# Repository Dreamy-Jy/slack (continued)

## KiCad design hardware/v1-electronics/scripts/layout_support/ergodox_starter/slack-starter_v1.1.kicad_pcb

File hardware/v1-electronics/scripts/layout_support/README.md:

This folder is a collection of code used to support the laying out of the keyboard components.

`ergogen_starter/` - is an [ergogen](https://ergogen.xyz/) config used to layout the base keyboard, most of this was ai generated.

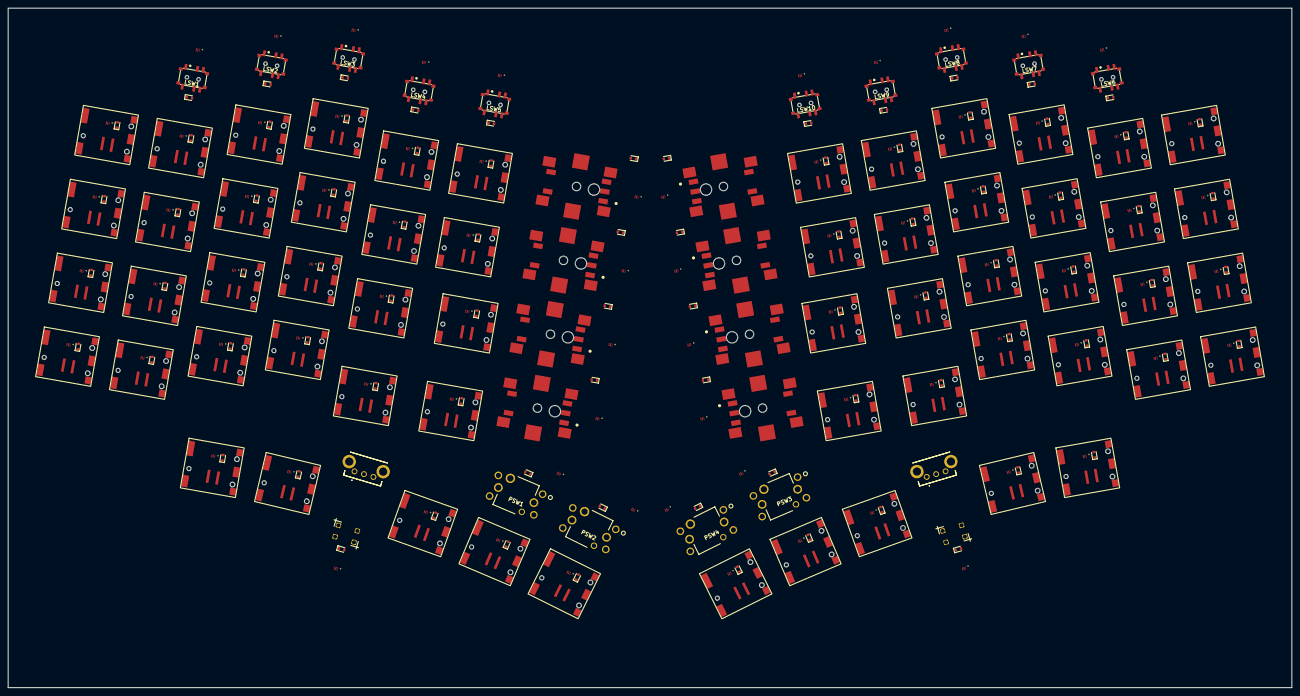
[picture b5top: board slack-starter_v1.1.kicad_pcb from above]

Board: 2 copper layers, 326.0 x 172.6 mm, 248 parts (0 on the bottom side), 165 nets, no tracks yet.

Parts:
D1, D2, D3, D4, D5, D6, D7, D8, D9, D10, D11, D12, D13, D14, D15, D16, D17, D18, D19, D20, D21, D22, D23, D24, D25, D26, D27, D28, D29, D30, D31, D32, D33, D34, D35, D36, D37, D38, D39, D40, D41, D42, D43, D44, D45, D46, D47, D48, D49, D50, D51, D52, D53, D54, D55, D56, D57, D58, D59, D60, D61, D62, D63, D64, D65, D66, D67, D68, D69, D70, D71, D72, D73, D74, D75, D76, D77, D78, D79, D80, D81, D82: D_SOD-523
ENC1, ENC2, ENC3, ENC4, ENC5, ENC6, ENC7, ENC8: PEC11S929KS0015
LED1, LED2, LED3, LED4, LED5, LED6, LED7, LED8, LED9, LED10, LED11, LED12, LED13, LED14, LED15, LED16, LED17, LED18, LED19, LED20, LED21, LED22, LED23, LED24, LED25, LED26, LED27, LED28, LED29, LED30, LED31, LED32, LED33, LED34, LED35, LED36, LED37, LED38, LED39, LED40, LED41, LED42, LED43, LED44, LED45, LED46, LED47, LED48, LED49, LED50, LED51, LED52, LED53, LED54, LED55, LED56, LED57, LED58, LED59, LED60, LED61, LED62, LED63, LED64, LED65, LED66, LED67, LED68, LED69, LED70, LED71, LED72, LED73, LED74, LED75, LED76, LED77, LED78, LED79, LED80, LED81, LED82: LTSTFC12WEGBD5A
LSW1, LSW2, LSW3, LSW4, LSW5, LSW6, LSW7, LSW8, LSW9, LSW10: SSSS820201
PSW1, PSW2, PSW3, PSW4: SPEF110100
S1, S2, S3, S4, S5, S6, S7, S8, S9, S10, S11, S12, S13, S14, S15, S16, S17, S18, S19, S20, S21, S22, S23, S24, S25, S26, S27, S28, S29, S30, S31, S32, S33, S34, S35, S36, S37, S38, S39, S40, S41, S42, S43, S44, S45, S46, S47, S48, S49, S50, S51, S52, S53, S54, S55, S56, S57, S58: Cherry_ULP_SMD
SCLK1, SCLK2: TC-1109-C-E
SCRL1, SCRL2: EC10E1220505

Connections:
C0: S1.1, S2.1, S3.1, S4.1, SCLK1.1
C1: LSW1.2, S5.1, S6.1, S7.1, S8.1, S25.1
C2: LSW2.2, S9.1, S10.1, S11.1, S12.1, S26.1
C3: LSW3.2, S13.1, S14.1, S15.1, S16.1, S27.1
C4: LSW4.2, S17.1, S18.1, S19.1, S20.1, S28.1
C5: LSW5.2, PSW1.1, S21.1, S22.1, S23.1, S24.1, S29.1
C6: LSW10.2, PSW2.1, S50.1, S51.1, S52.1, S53.1, S58.1
C7: LSW9.2, PSW4.1, S46.1, S47.1, S48.1, S49.1, S57.1
C8: LSW8.2, PSW3.1, S42.1, S43.1, S44.1, S45.1, S56.1
C9: LSW7.2, S38.1, S39.1, S40.1, S41.1, S55.1
C10: LSW6.2, S34.1, S35.1, S36.1, S37.1, S54.1
C11: S30.1, S31.1, S32.1, S33.1, SCLK2.1
ENCL: ENC1.D1, ENC2.D1, ENC3.D1, ENC4.D1
ENCR: ENC5.D1, ENC6.D1, ENC7.D1, ENC8.D1
GND: ENC1.C1, ENC2.C1, ENC3.C1, ENC4.C1, ENC5.C1, ENC6.C1, ENC7.C1, ENC8.C1, SCRL1.C1, SCRL2.C1
LED_C0_B: LED1.1, LED2.1, LED3.1, LED4.1, LED67.1
LED_C0_G: LED1.2, LED2.2, LED3.2, LED4.2, LED67.2
LED_C0_R: LED1.3, LED2.3, LED3.3, LED4.3, LED67.3
LED_C0_W: LED1.4, LED2.4, LED3.4, LED4.4, LED67.4
LED_C1_B: LED5.1, LED6.1, LED7.1, LED8.1, LED25.1, LED69.1
LED_C1_G: LED5.2, LED6.2, LED7.2, LED8.2, LED25.2, LED69.2
LED_C1_R: LED5.3, LED6.3, LED7.3, LED8.3, LED25.3, LED69.3
LED_C1_W: LED5.4, LED6.4, LED7.4, LED8.4, LED25.4, LED69.4
LED_C2_B: LED9.1, LED10.1, LED11.1, LED12.1, LED26.1, LED70.1
LED_C2_G: LED9.2, LED10.2, LED11.2, LED12.2, LED26.2, LED70.2
LED_C2_R: LED9.3, LED10.3, LED11.3, LED12.3, LED26.3, LED70.3
LED_C2_W: LED9.4, LED10.4, LED11.4, LED12.4, LED26.4, LED70.4
LED_C3_B: LED13.1, LED14.1, LED15.1, LED16.1, LED27.1, LED71.1
LED_C3_G: LED13.2, LED14.2, LED15.2, LED16.2, LED27.2, LED71.2
LED_C3_R: LED13.3, LED14.3, LED15.3, LED16.3, LED27.3, LED71.3
LED_C3_W: LED13.4, LED14.4, LED15.4, LED16.4, LED27.4, LED71.4
LED_C4_B: LED17.1, LED18.1, LED19.1, LED20.1, LED28.1, LED72.1
LED_C4_G: LED17.2, LED18.2, LED19.2, LED20.2, LED28.2, LED72.2
LED_C4_R: LED17.3, LED18.3, LED19.3, LED20.3, LED28.3, LED72.3
LED_C4_W: LED17.4, LED18.4, LED19.4, LED20.4, LED28.4, LED72.4
LED_C5_B: LED21.1, LED22.1, LED23.1, LED24.1, LED29.1, LED73.1, LED79.1
LED_C5_G: LED21.2, LED22.2, LED23.2, LED24.2, LED29.2, LED73.2, LED79.2
LED_C5_R: LED21.3, LED22.3, LED23.3, LED24.3, LED29.3, LED73.3, LED79.3
LED_C5_W: LED21.4, LED22.4, LED23.4, LED24.4, LED29.4, LED73.4, LED79.4
LED_C6_B: LED50.1, LED51.1, LED52.1, LED53.1, LED58.1, LED78.1, LED80.1
LED_C6_G: LED50.2, LED51.2, LED52.2, LED53.2, LED58.2, LED78.2, LED80.2
LED_C6_R: LED50.3, LED51.3, LED52.3, LED53.3, LED58.3, LED78.3, LED80.3
LED_C6_W: LED50.4, LED51.4, LED52.4, LED53.4, LED58.4, LED78.4, LED80.4
LED_C7_B: LED46.1, LED47.1, LED48.1, LED49.1, LED57.1, LED77.1, LED82.1
LED_C7_G: LED46.2, LED47.2, LED48.2, LED49.2, LED57.2, LED77.2, LED82.2
LED_C7_R: LED46.3, LED47.3, LED48.3, LED49.3, LED57.3, LED77.3, LED82.3
LED_C7_W: LED46.4, LED47.4, LED48.4, LED49.4, LED57.4, LED77.4, LED82.4
LED_C8_B: LED42.1, LED43.1, LED44.1, LED45.1, LED56.1, LED76.1, LED81.1
LED_C8_G: LED42.2, LED43.2, LED44.2, LED45.2, LED56.2, LED76.2, LED81.2
LED_C8_R: LED42.3, LED43.3, LED44.3, LED45.3, LED56.3, LED76.3, LED81.3
LED_C8_W: LED42.4, LED43.4, LED44.4, LED45.4, LED56.4, LED76.4, LED81.4
LED_C9_B: LED38.1, LED39.1, LED40.1, LED41.1, LED55.1, LED75.1
LED_C9_G: LED38.2, LED39.2, LED40.2, LED41.2, LED55.2, LED75.2
LED_C9_R: LED38.3, LED39.3, LED40.3, LED41.3, LED55.3, LED75.3
LED_C9_W: LED38.4, LED39.4, LED40.4, LED41.4, LED55.4, LED75.4
LED_C10_B: LED34.1, LED35.1, LED36.1, LED37.1, LED54.1, LED74.1
LED_C10_G: LED34.2, LED35.2, LED36.2, LED37.2, LED54.2, LED74.2
LED_C10_R: LED34.3, LED35.3, LED36.3, LED37.3, LED54.3, LED74.3
LED_C10_W: LED34.4, LED35.4, LED36.4, LED37.4, LED54.4, LED74.4
LED_C11_B: LED30.1, LED31.1, LED32.1, LED33.1, LED68.1
LED_C11_G: LED30.2, LED31.2, LED32.2, LED33.2, LED68.2
LED_C11_R: LED30.3, LED31.3, LED32.3, LED33.3, LED68.3
LED_C11_W: LED30.4, LED31.4, LED32.4, LED33.4, LED68.4
LED_ENCL_B: LED59.1, LED60.1, LED61.1, LED62.1
LED_ENCL_G: LED59.2, LED60.2, LED61.2, LED62.2
LED_ENCL_R: LED59.3, LED60.3, LED61.3, LED62.3
LED_ENCL_W: LED59.4, LED60.4, LED61.4, LED62.4
LED_ENCR_B: LED63.1, LED64.1, LED65.1, LED66.1
LED_ENCR_G: LED63.2, LED64.2, LED65.2, LED66.2
LED_ENCR_R: LED63.3, LED64.3, LED65.3, LED66.3
LED_ENCR_W: LED63.4, LED64.4, LED65.4, LED66.4
LED_R0: LED4.5, LED8.5, LED12.5, LED16.5, LED20.5, LED24.5, LED33.5, LED37.5, LED41.5, LED45.5, LED49.5, LED53.5, LED62.5, LED66.5
LED_R1: LED3.5, LED7.5, LED11.5, LED15.5, LED19.5, LED23.5, LED32.5, LED36.5, LED40.5, LED44.5, LED48.5, LED52.5, LED61.5, LED65.5
LED_R2: LED2.5, LED6.5, LED10.5, LED14.5, LED18.5, LED22.5, LED31.5, LED35.5, LED39.5, LED43.5, LED47.5, LED51.5, LED60.5, LED64.5
LED_R3: LED1.5, LED5.5, LED9.5, LED13.5, LED17.5, LED21.5, LED30.5, LED34.5, LED38.5, LED42.5, LED46.5, LED50.5, LED59.5, LED63.5
LED_R4: LED25.5, LED26.5, LED27.5, LED28.5, LED29.5, LED54.5, LED55.5, LED56.5, LED57.5, LED58.5, LED67.5, LED68.5
LED_R5: LED69.5, LED70.5, LED71.5, LED72.5, LED73.5, LED74.5, LED75.5, LED76.5, LED77.5, LED78.5, LED79.5, LED80.5, LED81.5, LED82.5
R0: D4.1, D8.1, D12.1, D16.1, D20.1, D24.1, D33.1, D37.1, D41.1, D45.1, D49.1, D53.1, D64.1, D68.1
R1: D3.1, D7.1, D11.1, D15.1, D19.1, D23.1, D32.1, D36.1, D40.1, D44.1, D48.1, D52.1, D63.1, D67.1
R2: D2.1, D6.1, D10.1, D14.1, D18.1, D22.1, D31.1, D35.1, D39.1, D43.1, D47.1, D51.1, D62.1, D66.1
R3: D1.1, D5.1, D9.1, D13.1, D17.1, D21.1, D30.1, D34.1, D38.1, D42.1, D46.1, D50.1, D61.1, D65.1
R4: D25.1, D26.1, D27.1, D28.1, D29.1, D54.1, D55.1, D56.1, D57.1, D58.1, D59.1, D60.1
R5: D69.1, D70.1, D71.1, D72.1, D73.1, D74.1, D75.1, D76.1, D77.1, D78.1, D79.1, D80.1, D81.1, D82.1
col_bottom: D61.2, ENC1.E1
col_home: D62.2, ENC2.E1
col_num: D64.2, ENC4.E1
col_top: D63.2, ENC3.E1
index_bottom: D17.2, S17.2
index_home: D18.2, S18.2
index_num: D20.2, S20.2
index_row: D72.2, LSW4.1
index_top: D19.2, S19.2
inner_bottom: D21.2, S21.2
inner_home: D22.2, S22.2
inner_num: D24.2, S24.2
inner_row: D73.2, LSW5.1
inner_top: D23.2, S23.2
lk4_row: D79.2, PSW1.2
lk5_row: D80.2, PSW2.2
middle_bottom: D13.2, S13.2
middle_home: D14.2, S14.2
middle_num: D16.2, S16.2
middle_row: D71.2, LSW3.1
middle_top: D15.2, S15.2
mirror_col_bottom: D65.2, ENC5.E1
mirror_col_home: D66.2, ENC6.E1
mirror_col_num: D68.2, ENC8.E1
mirror_col_top: D67.2, ENC7.E1
mirror_index_bottom: D46.2, S46.2
mirror_index_home: D47.2, S47.2
mirror_index_num: D49.2, S49.2
mirror_index_row: D77.2, LSW9.1
mirror_index_top: D48.2, S48.2
mirror_inner_bottom: D50.2, S50.2
mirror_inner_home: D51.2, S51.2
mirror_inner_num: D53.2, S53.2
mirror_inner_row: D78.2, LSW10.1
mirror_inner_top: D52.2, S52.2
mirror_lk4_row: D81.2, PSW3.2
mirror_lk5_row: D82.2, PSW4.2
mirror_middle_bottom: D42.2, S42.2
mirror_middle_home: D43.2, S43.2
mirror_middle_num: D45.2, S45.2
mirror_middle_row: D76.2, LSW8.1
mirror_middle_top: D44.2, S44.2
mirror_outer_bottom: D30.2, S30.2
mirror_outer_home: D31.2, S31.2
mirror_outer_num: D33.2, S33.2
mirror_outer_top: D32.2, S32.2
mirror_pinky_bottom: D34.2, S34.2
mirror_pinky_home: D35.2, S35.2
mirror_pinky_num: D37.2, S37.2
mirror_pinky_row: D74.2, LSW6.1
mirror_pinky_top: D36.2, S36.2
mirror_ring_bottom: D38.2, S38.2
mirror_ring_home: D39.2, S39.2
mirror_ring_num: D41.2, S41.2
mirror_ring_row: D75.2, LSW7.1
mirror_ring_top: D40.2, S40.2
mirror_scroll_cluster: D60.2, SCLK2.4
mirror_t1_cluster: D54.2, S54.2
mirror_t2_cluster: D55.2, S55.2
mirror_t3_cluster: D56.2, S56.2
mirror_t4_cluster: D57.2, S57.2
mirror_t5_cluster: D58.2, S58.2
outer_bottom: D1.2, S1.2
outer_home: D2.2, S2.2
outer_num: D4.2, S4.2
outer_top: D3.2, S3.2
pinky_bottom: D5.2, S5.2
pinky_home: D6.2, S6.2
pinky_num: D8.2, S8.2
pinky_row: D69.2, LSW1.1
pinky_top: D7.2, S7.2
ring_bottom: D9.2, S9.2
ring_home: D10.2, S10.2
ring_num: D12.2, S12.2
ring_row: D70.2, LSW2.1
ring_top: D11.2, S11.2
scroll_cluster: D59.2, SCLK1.4
t1_cluster: D25.2, S25.2
t2_cluster: D26.2, S26.2
t3_cluster: D27.2, S27.2
t4_cluster: D28.2, S28.2
t5_cluster: D29.2, S29.2

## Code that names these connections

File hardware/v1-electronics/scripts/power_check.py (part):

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        stop=100000,
        step=100,
        value=22000,
        label="LED driver R_EXT (Ω, R41/R45)",
    )
    gcc = mo.ui.slider(
        start=1,
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        stop=50,
        step=0.5,
        value=6.0,
        label="PMID cap C49 effective (µF, 10 µF nominal)",
    )
    c_sys = mo.ui.number(
        start=0,
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        stop=100,
        step=0.5,
        value=6.0,
        label="BATT cap C50 effective (µF, 10 µF nominal)",
    )
    c_bst = mo.ui.number(
        start=0,
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
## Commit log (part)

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2026-02-11 checkpoint: initial commit
2026-02-11 docs: add to do list
2026-02-20 docs: updated to dos and documented progress
2026-02-20 docs: add to do
2026-03-22 docs: update to dos and plan
2026-04-09 checkpoint: pre ai commit
2026-04-24 fix(v1 hardware): Started and Ammended the hardware design.
    We're using the Raytac MDBT50Q-1MV2 instead of the nice!nano, due to a
    lack of exposed digial IO.
    The Kicad for the hardware are not in this commit because I need to
    figure out git for them.
    We started using the seb coding agent in the project.
    prior plans that changed:
2026-04-24 feat(v1 hardware): implement switch matrix
2026-04-25 feat(v1 hardware): complete matrix schematic
    I added the filters for the all the encoders
    I will need to add the latching buttons in the future. For now the
    latches have been excluding from the schematic all together. I think the
    best way to add them would be to add another row to the matrix, that is
    only latches.
2026-04-26 feat(v1 hardware): added usb-c and select mcu power mode
2026-04-30 feat(v1 hardware): add simple power circuitry
    I've added simple power circuitry. It does not do everything I want but
    it's a start.
2026-05-02 feat(v1 hardware): LED Matrix
    - added symbols and footprints for leds and their matrix ic.
    - modified symbols for leds.
    - started schematic for matrix ic and led matrix
2026-05-02 docs: update
    I changed a bunch of docs. Unsure of what the changes are but I'm adding
    them all.
2026-05-04 feat(v1 hardware): LED Matrix refactor start
    - refactored RGBW LED schematic symbol.
    - realize that IS31FL3741A will need to be replaced.
2026-05-04 feat(v1 hardware): Add new LED Matrix driver
    - added the symbol for 3733
    - added circuit for 3733
    - have not removed: old matrix and 3741A symbol & circuits
2026-05-05 feat(v1 hardware): RGBW LED matrix halve 1
2026-05-05 feat(v1 hardware):second half of LED Matrix
2026-05-05 support(v1 hardware): introduce scripts
    introduced a pixi script repo to help with KiCad edits.
2026-05-05 feat(v1 hardware): clean up led matrix
2026-05-05 feat(v1 hardware): start assigning pins on th mcu
2026-05-06 feat(v1 hardware): refine controller schematic
2026-05-07 refactor(v1 hardware): power train
2026-05-10 refactor(v1 hardware): add different charger ic & clean-up schematics
2026-05-16 fix(v1 hardware): fixed the matrix circuit
    the change in LED Matrix Driver results in a need to change how we
    wire the matrix. this diff accounts for that.
    i needed to use a script to rename labels.
2026-05-23 refactor(v1 hardware): power system
    Beefed up power system.
2026-05-24 refactor(v1 hardware): power train part 2
2026-05-24 refactor(v1 hardware): power system refactor complete
    - changed components and cleaned up schematic
2026-05-31 feat(v1 hardware): add protection to usb-c port
    added ESD protection and EMI filtering
    start assigning values to passive components
2026-06-14 feat(v1 hardware): select passives values
2026-06-20 refactor(v1 hardware): convert switch matrix to hierarchical pins
    made other changes
    had claude generate a script for making the convertion
    the references for this file still need to be fixed
2026-06-20 refactor(v1 hardware): led matrix now uses hierarchical labels
2026-06-20 refactor(v1 hardware): all sheets now use hierarchical labels
    We'll might change these to buses down the line, but we'll see
    I'm happy for now
2026-06-21 refactor(v1 hardware): root level schematic is made discriptive with hierarchical pins
2026-06-21 refactor(v1 hardware): transition to hierarchical pins complete
    All the buses renamed to stuff
2026-06-22 refactor(v1 hardware): refactored led controllers into a seperate sheet
2026-06-22 checkpoint(v1 hardware)
    not sure what changed
2026-06-22 doc(v1 hardware): start writting based on work
2026-06-24 refactor(v1 hardware): get references in order
